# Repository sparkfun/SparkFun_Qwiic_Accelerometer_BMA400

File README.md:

SparkFun Triple Axis Accelerometer Breakout - BMA400 (Qwiic) 
============================================================

<table class="table table-striped table-bordered"?
  <tr align="center">
    <td></td>
    <td></td>
  </tr>
  <tr align="center">
    <td><a href="https://www.sparkfun.com/products/21208"><i>SparkFun Triple Axis Accelerometer Breakout - BMA400 (Qwiic)</i></a></td>
    <td><a href="https://www.sparkfun.com/products/21207"><i>SparkFun Micro Triple Axis Accelerometer Breakout - BMA400 (Qwiic)</i></a></td>
  </tr>
</table>

The SparkFun Qwiic BMA400 Triple Axis Accelerometer Breakout offers a 3-axis acceleration sensor perfect for ultra-low-power applications on an easy-to-use Qwiic breakout board. Dubbed the first "real" ultra-low power acceleration sensor, the BMA400 is perfect when used in both wearable and smart home applications. Where this sensor shines, however, is its ability to distinguish between critical situations and false signals by avoiding false alarms. The Qwiic system allows for integration into your I<sup>2</sup>C system with no soldering required. This Qwiic breakout also includes 0.1"-spaced PTH pins connected to the sensor's communication interface and interrupt pins for applications that require a traditional soldered connection.

The BMA400 from Bosch Sensortech<sup>&copy;</sup> has a full-scale acceleration range of &plusmn;2/&plusmn;4/&plusmn;8/&plusmn;16g with exceptionally low current consumption of < 14.5&micro;A while operating at its highest performance settings. The sensor also includes a complete feature set for on-chip interrupts including auto wakeup/low power, step counter, activity recognition, orientation detection, and tap/double tap. 

Repository Contents
-------------------
* **/Documents** - Datasheet
* **/Hardware** - Eagle design files (.brd, .sch)
* **/Production** - Production panel files (.brd)

Documentation
-------------
* **[Hookup Guide](https://learn.sparkfun.com/tutorials/sparkfun-triple-axis-accelerometer-breakout---bma400-qwiic-hookup-guide)** - Basic Hookup Guide for the SparkFun Triple Axis Accelerometer Breakout - BMA400 (Qwiic). 
* **[BMA400 Arduino Library](https://github.com/sparkfun/SparkFun_BMA400_Arduino_Library)** - Arduino library for the BMA400 based off the Bosch API.

Product Versions
----------------
* [SEN-21208](https://www.sparkfun.com/products/21208) - Standard Size Initial Release.
* [SEN-21207](https://www.sparkfun.com/products/21207) - Micro Size Initial Release.

License Information
-------------------

This product is _**open source**_! 

Please review the LICENSE.md file for license information.

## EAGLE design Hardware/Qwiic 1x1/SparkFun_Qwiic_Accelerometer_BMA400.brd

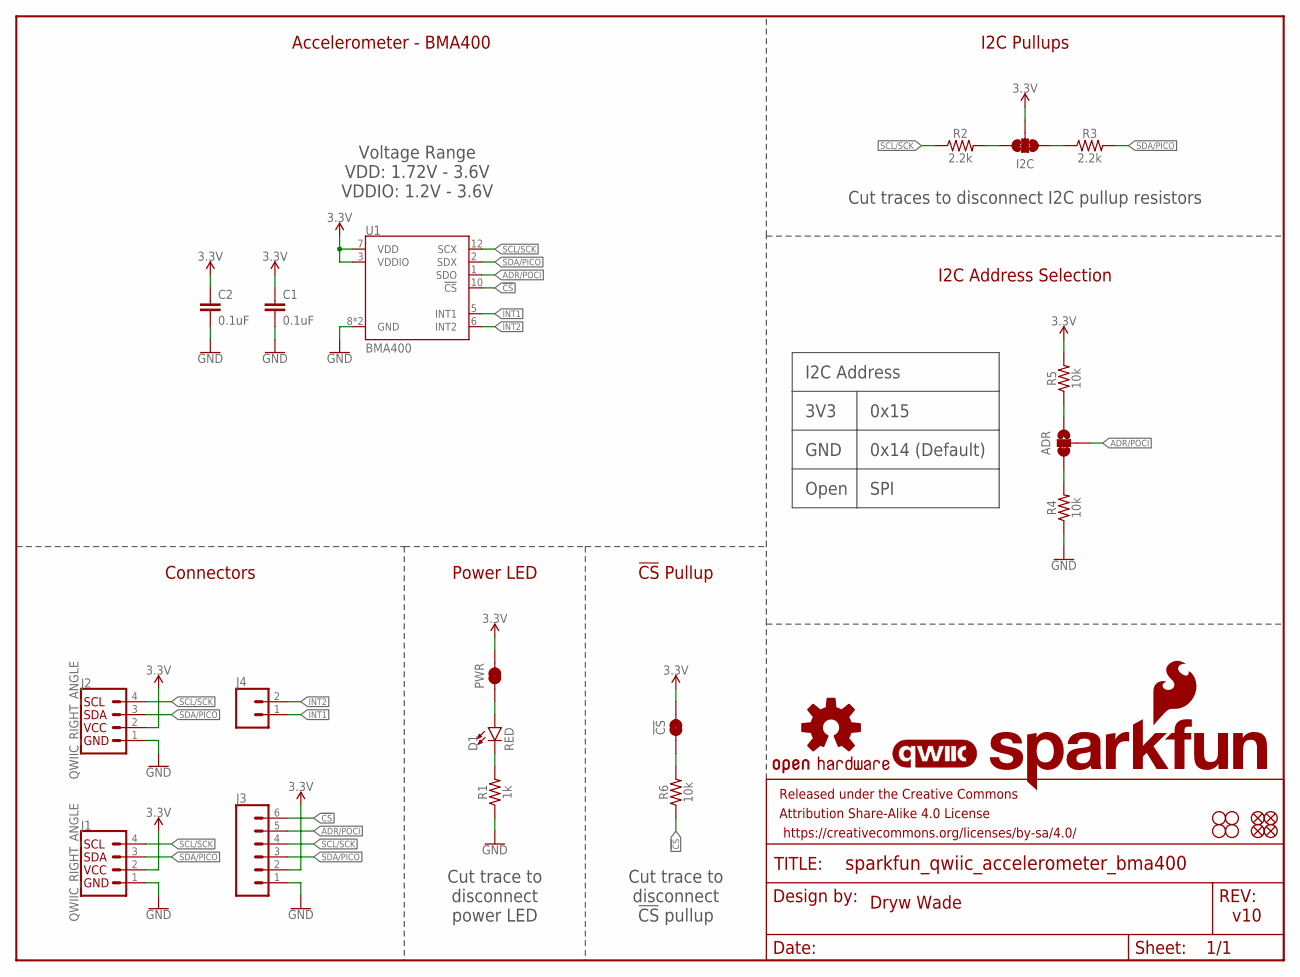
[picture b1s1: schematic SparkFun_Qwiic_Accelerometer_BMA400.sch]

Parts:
!CS!: JUMPER-SMT_2_NC_TRACE_SILK; SMT-JUMPER_2_NC_TRACE_SILK
ADR: JUMPER-SMT_3_1-NC_TRACE_SILK; SMT-JUMPER_3_1-NC_TRACE_SILK
C1, C2: 0.1uF; 0603
D1: RED; LED-0603
FD1, FD2, FD3, FD4: FIDUCIAL1X2; FIDUCIAL-1X2
FRAME1: FRAME-LETTER; CREATIVE_COMMONS
H1, H2, H3, H4: STAND-OFF
I2C: JUMPER-SMT_3_2-NC_TRACE_SILK; SMT-JUMPER_3_2-NC_TRACE_SILK
J1, J2: QWIIC_RIGHT_ANGLE; JST04_1MM_RA
J3: CONN_06NO_SILK_NO_POP; 1X06_NO_SILK
J4: CONN_021X02_NO_SILK; 1X02_NO_SILK
LOGO1: QWIIC_LOGO_5MM; QWIIC_5MM
LOGO2: SFE_LOGO_NAME_FLAME.1_INCH; SFE_LOGO_NAME_FLAME_.1
LOGO3: OSHW-LOGOS; OSHW-LOGO-S
PWR: JUMPER-SMT_2_NC_TRACE_SILK; SMT-JUMPER_2_NC_TRACE_SILK
R1: 1k; 0603
R2, R3: 2.2k; 0603
R4, R5, R6: 10k; 0603
U1: BMA400

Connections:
3.3V: !CS!.2, C1.1, C2.1, I2C.2, J1.2, J2.2, J3.2, PWR.2, R5.2, U1.3 (VDDIO), U1.7 (VDD)
!CS!: J3.6, R6.1, U1.10 (!CS!)
ADR/POCI: ADR.2, J3.5, U1.1 (SDO)
GND: C1.2, C2.2, J1.1, J2.1, J3.1, R1.1, R4.1, U1.8 (GND), U1.9 (GND)
INT1: J4.1, U1.5 (INT1)
INT2: J4.2, U1.6 (INT2)
unnamed: D1.A, PWR.1
unnamed: D1.C, R1.2
unnamed: I2C.3, R2.2
unnamed: I2C.1, R3.1
unnamed: ADR.1, R5.1
unnamed: ADR.3, R4.2
unnamed: !CS!.1, R6.2
SCL/SCK: J1.4, J2.4, J3.4, R2.1, U1.12 (SCX)
SDA/PICO: J1.3, J2.3, J3.3, R3.2, U1.2 (SDX)

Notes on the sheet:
Dryw Wade
v10
Accelerometer - BMA400
Connectors
Power LED
I2C Pullups
I2C Address Selection
I2C Address
GND
3V3
Open
0x15
0x14 (Default)
SPI
Cut traces to disconnect I2C pullup resistors
Cut trace to disconnect power LED
!CS! Pullup
Cut trace to disconnect !CS! pullup
Voltage Range VDD: 1.72V - 3.6V VDDIO: 1.2V - 3.6V

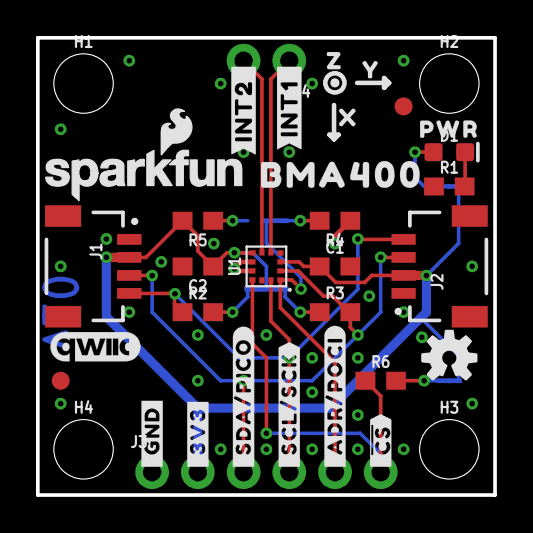
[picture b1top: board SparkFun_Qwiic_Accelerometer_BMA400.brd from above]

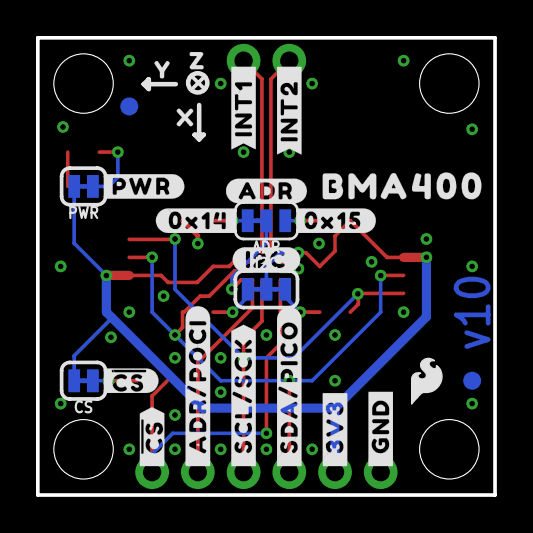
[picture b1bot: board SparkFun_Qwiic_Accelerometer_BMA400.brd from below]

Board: 2 copper layers, 25.4 x 25.4 mm, 62 parts (25 on the bottom side), 15 nets.

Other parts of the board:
U$1: PWR0
U$2, U$34: X2114
U$3, U$35: Y2115
U$4, U$20: #INT1_#0
U$5, U$21: #INT2_#0
U$6: #_3V3#6
U$7: #_SDA#PICO#5
U$8: #_#CS##2
U$9: #_SCL#SCK#3
U$10: #_GND#0
U$11: #_3V3#0
U$12: #_SDA#PICO#0
U$13: #_SCL#SCK#0
U$14: #_ADR#POCI#0
U$15: #_#CS##0
U$16: #I2C#0
U$17: #ADR#0
U$18: #0X15#0
U$19: #0X14#0
U$22: #PWR#0
U$23, U$24: BMA4000
U$25: ##CS##0
U$26: SFE_LOGO_FLAME_.1
U$27: #_ADR#POCI#1
U$28: #_GND#6
U$29, U$36: Z2116

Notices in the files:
parts and their libraries:
SparkFun-Aesthetics: Licensing: Creative Commons ShareAlike 4.0 International - https://creativecommons.org/licenses/by-sa/4.0
SparkFun-Aesthetics: Released under the Creative Commons Attribution Share-Alike 4.0 License
SparkFun-Aesthetics: https://creativecommons.org/licenses/by-sa/4.0
